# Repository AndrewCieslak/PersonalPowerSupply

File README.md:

# PersonalPowerSupply

My personal 20V in, 15-1.5 V out buck converter power supply code and schematics. Fully discrete, with almost no integrated components for the feedback loop.

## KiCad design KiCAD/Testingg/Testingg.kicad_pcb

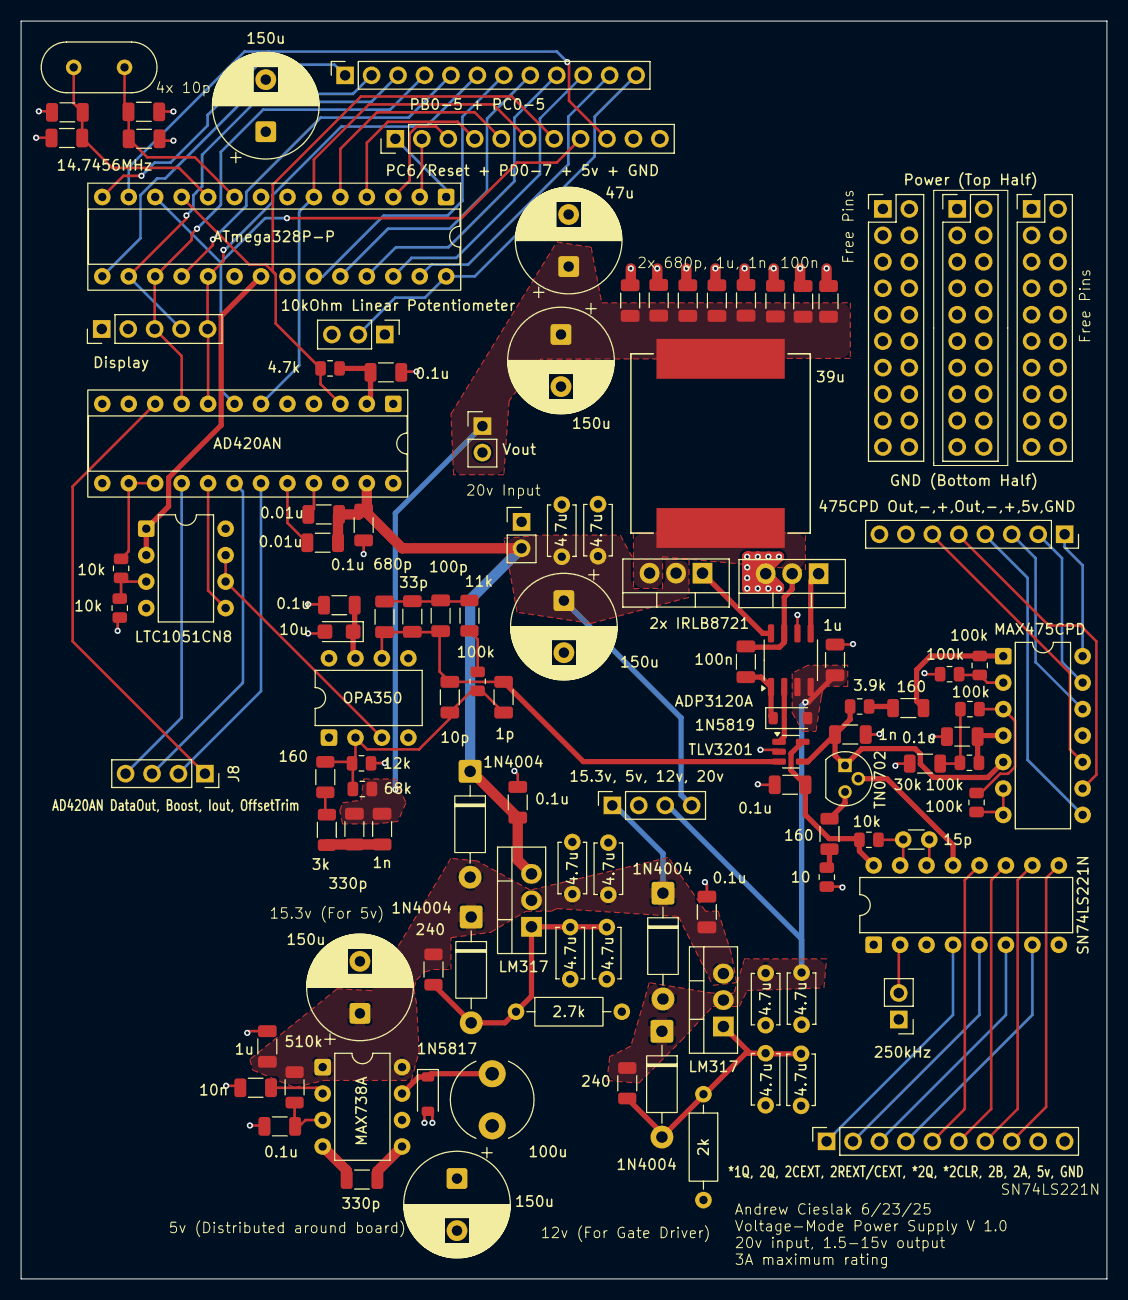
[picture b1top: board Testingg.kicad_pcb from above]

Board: 4 copper layers, 104.3 x 120.8 mm, 115 parts (0 on the bottom side), 84 nets.

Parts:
C1, C3, C8, C15, C16, C17, C22: 0.1u; C_1206_3216Metric
C2, C11, C12, C13, C18, C20, C21, C25: 4.7u; C_Disc_D4.7mm_W2.5mm_P5.00mm
C4: 330p; C_1206_3216Metric
C5, C10: 1u; C_1206_3216Metric
C6, C7, C14: 150u; CP_Radial_D10.0mm_P5.00mm
C9: 10n; C_1206_3216Metric
C19: 100n; C_1206_3216Metric
C23: 10u; CP_EIA-3216-10_Kemet-I
C24: 1n; C_1206_3216Metric
C26: 15p; C_Disc_D3.0mm_W1.6mm_P2.50mm
Cadnpo1, Cadnpo2: 0.01u; C_1206_3216Metric
Cbypass2: 0.1u; C_1206_3216Metric
Ccomp1: 100p; C_1206_3216Metric
Ccomp2: 33p; C_1206_3216Metric
Ccomp4: 680p; C_1206_3216Metric
Cff1: 1n; C_1206_3216Metric
Cff2: 330p; C_1206_3216Metric
Chf1: 10p; C_1206_3216Metric
Chf4: 1p; C_1206_3216Metric
Cin1, Cin2: 4.7u; C_Disc_D4.7mm_W2.5mm_P5.00mm
Cin3: 150u; CP_Radial_D10.0mm_P5.00mm
Cout1: 150u; CP_Radial_D10.0mm_P5.00mm
Cout2: 47u; CP_Radial_D10.0mm_P5.00mm
Cout3, Cout4: 1u; C_1206_3216Metric
Cout5, Cout6: 0.1u; C_1206_3216Metric
Cout7, Cout8: 1n; C_1206_3216Metric
Cout9, Cout10: 680p; C_1206_3216Metric
Cxtal1, Cxtal2, Cxtal3, Cxtal4: 10p; C_1206_3216Metric
D1: 1N5817; D_SOD-123
D2, D4, D5, D6: 1N4004; D_DO-41_SOD81_P10.16mm_Horizontal
D3: 1N5819; D_SOD-123
Display1: Display; PinHeader_1x05_P2.54mm_Vertical
J1: 10kOhm Linear Potentiometer; PinHeader_1x03_P2.54mm_Vertical
J2: 15.3v, 5v, 12v, 20v; PinSocket_1x04_P2.54mm_Vertical
J3: *1Q, 2Q, 2CEXT, 2REXT/CEXT, *2Q, *2CLR, 2B, 2A, 5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; PinSocket_1x10_P2.54mm_Vertical
J4: PB0-5 + PC0-5; PinSocket_1x12_P2.54mm_Vertical
J5: 250kHz; PinHeader_1x02_P2.54mm_Vertical
J6: Vin; PinHeader_1x02_P2.54mm_Vertical
J7: Breadboard; PinHeader_2x10_P2.54mm_Vertical
J8: AD420AN DataOut, Boost, Iout, OffsetTrim; PinSocket_1x04_P2.54mm_Vertical
J9: PC6/Reset + PD0-7 + 5v + GND; PinHeader_1x11_P2.54mm_Vertical
J10: 475CPD Out,-,+,Out,-,+,5v,GND; PinSocket_1x08_P2.54mm_Vertical
J11: Power (Top Half); PinHeader_2x10_P2.54mm_Vertical
J12: Breadboard2; PinHeader_2x10_P2.54mm_Vertical
L1: 100u; L_Radial_D7.8mm_P5.00mm_Fastron_07HCP
Lmain1: 39u; L_Vishay_IHLP-6767
Q1: IRLB8721PBF; TO-220-3_Vertical
Q2: 2x IRLB8721; TO-220-3_Vertical
R1, R4: 160; R_1206_3216Metric
R2: 10; R_0805_2012Metric
R3: 3.9k; R_0805_2012Metric
R5, R18, R19, R20, R21: 100k; R_0805_2012Metric
R6: 30k; R_1206_3216Metric
R7, R10: 240; R_1206_3216Metric
R8: 2.7k; R_Axial_DIN0207_L6.3mm_D2.5mm_P10.16mm_Horizontal
R9: 2k; R_Axial_DIN0207_L6.3mm_D2.5mm_P10.16mm_Horizontal
R14: 68k; R_0805_2012Metric
R15: 12k; R_0805_2012Metric
R16: 510k; R_1206_3216Metric
R24: 10k; R_0805_2012Metric
Rcomp1: 11k; R_1206_3216Metric
Rcomp3: 100k; R_0805_2012Metric
Rdiv1, Rdiv2: 10k; R_0805_2012Metric
Rff1: 160; R_1206_3216Metric
Rff2: 3k; R_1206_3216Metric
RpullupU6: 4.7k; R_0805_2012Metric
U1, U2: LM317; TO-220-3_Vertical
U3: ADP3120A; SO-8_3.9x4.9mm_P1.27mm
U4: OPA350; DIP-8_W7.62mm
U5: ATmega328P-P; DIP-28_W7.62mm_Socket
U6: AD420AN; DIP-24_W7.62mm_Socket
U7: LTC1051CN8; DIP-8_W7.62mm
U11: MAX738A; DIP-8_W7.62mm
U14: MAX475CPD; DIP-14_W7.62mm
U15: TN0702; TO-92
U17: SN74LS221N; DIP-16_W7.62mm
VM1: TLV3201; SOT-23-5
Vout1: Vout; PinHeader_1x02_P2.54mm_Vertical
Y1: 14.7456MHz; Crystal_HC49-U_Vertical

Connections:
+5V: C3.1, C4.2, C6.1, C14.1, C15.2, C22.1, C23.1, Cbypass2.1, Display1.1, J1.3, J2.2, J3.9, J9.10, J10.7, J11.1, J11.2, J11.3, J11.4, J11.5, J11.6, J11.7, J11.8, J11.9, J11.10, L1.2, R5.2, R24.1, RpullupU6.1, U4.7 (V+), U5.7 (VCC), U5.20 (AVCC), U6.2 (VLL), U7.8 (V+), U11.5 (OUT), U14.4 (V+), U17.3 (*1CLR), U17.16 (VCC), VM1.5 (VCC)
+20V: C16.2, C17.2, Cadnpo1.2, Cadnpo2.2, Cin1.1, Cin2.1, Cin3.1, D4.1 (K), J2.4, J6.2, Q2.2 (D), U1.3 (VI), U6.23 (VCC)
/J1: J4.1, U5.14 (PB0)
/J2: J4.2, U5.15 (PB1)
/J3: Display1.4, J4.3, U5.16 (PB2)
/J4: Display1.3, J4.4, U5.17 (PB3), U6.9 (DATA_IN)
/J5: J4.5, U5.18 (PB4)
/J6: Display1.5, J4.6, U5.19 (PB5), U6.8 (CLOCK)
/J9: J4.9, U5.25 (PC2)
/J10: J4.10, U5.26 (PC3)
/J11: J4.11, U5.27 (PC4)
/J12: J1.2, J4.12, U5.28 (PC5)
/VrefVM: U4.3 (IN+), U7.6 (IN_B-), U7.7 (OUT_B)
Earth: C1.1, C2.2, C3.2, C5.1, C6.2, C7.2, C8.1, C9.1, C10.2, C11.2, C12.2, C13.2, C14.2, C15.1, C16.1, C17.1, C18.2, C20.2, C21.2, C22.2, C23.2, C24.1, C25.2, Cbypass2.2, Cin1.2, Cin2.2, Cin3.2, Cout1.2, Cout2.2, Cout3.2, Cout4.2, Cout5.2, Cout6.2, Cout7.2, Cout8.2, Cout9.2, Cout10.2, Cxtal1.2, Cxtal2.2, Cxtal3.2, Cxtal4.2, D1.2 (A), Display1.2, J1.1, J3.10, J5.1, J6.1, J9.11, J10.8, J11.11, J11.12, J11.13, J11.14, J11.15, J11.16, J11.17, J11.18, J11.19, J11.20, Q1.3 (S), R2.1, R6.1, R8.2, R9.2, R15.2, R19.2, Rdiv2.1, U3.6 (PGND), U4.4 (V-), U5.8 (GND), U5.22 (GND), U6.4 (RANGE_SELECT2), U6.5 (RANGE_SELECT1), U6.11 (GND), U7.4 (V-), U11.6 (GND), U14.11 (V-), U17.1 (1A), U17.8 (GND), VM1.2 (GND), Vout1.2
unnamed: Ccomp1.2, Ccomp2.2, Ccomp4.2, Rcomp1.1
unnamed: Cff1.1, Cff2.1, Rff2.2
unnamed: D1.1 (K), L1.1, U11.7 (LX)
unnamed: C10.1, C12.1, C13.1, D2.2 (A), D3.2 (A), D6.1 (K), J2.3, R10.1, U2.2 (VO), U3.3 (*OD), U3.4 (VCC)
unnamed: C1.2, C5.2, C7.1, C21.1, C25.1, D2.1 (K), D4.2 (A), D5.1 (K), J2.1, R7.1, R16.1, U1.2 (VO), U2.3 (VI), U11.1 (*SHDN), U11.8 (V+)
unnamed: C19.2, D3.1 (K), U3.1 (BST)
unnamed: C18.1, C20.1, D5.2 (A), R7.2, R8.1, U1.1 (ADJ)
unnamed: C2.1, C11.1, D6.2 (A), R9.1, R10.2, U2.1 (ADJ)
unnamed: J3.1, U17.4 (*1Q)
unnamed: J3.2, U17.5 (2Q)
unnamed: J3.3, U17.6 (2CEXT)
unnamed: J3.4, U17.7 (2REXT/CEXT)
unnamed: J3.5, U17.12 (*2Q)
unnamed: J3.6, U17.11 (*2CLR)
unnamed: J3.7, U17.10 (2B)
unnamed: J3.8, U17.9 (2A)
unnamed: J4.7, U5.23 (PC0)
unnamed: J4.8, U5.24 (PC1)
unnamed: J5.2, U17.2 (1B)
unnamed: J8.1, U6.10 (DATA_OUT)
unnamed: J8.2, U6.19 (BOOST)
unnamed: J8.3, U6.18 (IOUT)
unnamed: J8.4, U6.16 (OFFSET_TRIM)
unnamed: J9.1, U5.1 (~RESET/PC6)
unnamed: J9.2, U5.2 (PD0)
unnamed: J9.3, U5.3 (PD1)
unnamed: J9.4, U5.4 (PD2)
unnamed: J9.5, U5.5 (PD3)
unnamed: J9.6, U5.6 (PD4), U6.6 (CLEAR)
unnamed: J9.7, RpullupU6.2, U5.11 (PD5), U6.3 (FAULT_DETECT)
unnamed: J9.8, U5.12 (PD6), U6.7 (LATCH)
unnamed: J9.9, U5.13 (PD7)
unnamed: J10.1, U14.14 (OUT)
unnamed: J10.2, U14.13 (-)
unnamed: J10.3, U14.12 (+)
unnamed: J10.4, U14.8 (OUT)
unnamed: J10.5, U14.9 (-)
unnamed: J10.6, U14.10 (+)
unnamed: C19.1, Lmain1.1, Q1.2 (D), Q2.3 (S), U3.7 (SWN)
unnamed: Q1.1 (G), U3.5 (DRVL)
unnamed: Q2.1 (G), U3.8 (DRVH)
unnamed: R1.1, R2.2
unnamed: R3.1, R4.1
unnamed: R18.1, R19.1, U14.2 (-)
unnamed: R4.2, R18.2, U14.1 (OUT)
unnamed: R5.1, R6.2, R20.1
unnamed: R20.2, R21.2, U14.3 (+)
unnamed: R21.1, U14.6 (-), U14.7 (OUT)
unnamed: Rcomp1.2, Rcomp3.1
unnamed: Rff1.2, Rff2.1
unnamed: U3.2 (IN), VM1.1 (OUT)
unnamed: Chf1.2, Chf4.2, R14.1, R15.1, Rcomp3.2, Rff1.1, U4.2 (IN-)
unnamed: Ccomp1.1, Ccomp2.1, Ccomp4.1, Chf1.1, Chf4.1, U4.6 (OUTPUT), VM1.3 (IN+)
unnamed: U5.21 (AREF), U7.1 (OUT_A), U7.2 (IN_A-)
unnamed: Cxtal2.1, Cxtal3.1, U5.9 (XTAL1/PB6), Y1.2
unnamed: Cxtal1.1, Cxtal4.1, U5.10 (XTAL2/PB7), Y1.1
unnamed: Cadnpo1.1, U6.20 (CAP1)
unnamed: Cadnpo2.1, U6.21 (CAP2)
unnamed: Rdiv1.2, U6.14 (REF_OUT), U6.15 (REF_IN)
unnamed: U6.17 (VOUT), U7.5 (IN_B+)
unnamed: Rdiv1.1, Rdiv2.2, U7.3 (IN_A+)
unnamed: C4.1, U11.4 (CC)
unnamed: C9.2, U11.2 (REF)
unnamed: C8.2, R16.2, U11.3 (SS)
unnamed: R1.2, U15.3 (DRAIN)
unnamed: U15.2 (GATE), U17.13 (1Q)
unnamed: C24.2, R3.2, U14.5 (+), U15.1 (SOURCE), VM1.4 (IN-)
unnamed: C26.1, U17.14 (1CEXT)
unnamed: C26.2, R24.2, U17.15 (1REXT/CEXT)
unnamed: Cff1.2, Cff2.2, Cout1.1, Cout2.1, Cout3.1, Cout4.1, Cout5.1, Cout6.1, Cout7.1, Cout8.1, Cout9.1, Cout10.1, Lmain1.2, R14.2, Vout1.1

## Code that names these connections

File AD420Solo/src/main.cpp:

#include <avr/io.h>
#include <util/delay.h>
#include <stdint.h>

#include "pins.h"
#include "uart.h"



int main(void){

  uart_init();
  
  //LEDs
  DDRD |= (1<<PD2) | (1<<PD3) | (1<<PD5);
  PORTD &= ~((1<<PD2) | (1<<PD3) | (1<<PD5));
  //blue LED ON
  PORTD |= (1<<PD2);

  DDRB  |= (1<<PB3) | (1<<PB5);
  PORTB |= (1<<PB2);
  SPCR = (1<<SPE) | (1<<MSTR);
  SPSR = 0;   
  AD420_CLR_DDR |= (1<<CLR_AD420);
  AD420_CLR_PORT &= ~(1<<CLR_AD420);
  // SPI init

  AD420_CLR_PORT |=  (1<<CLR_AD420);   // CLEAR = 1
  _delay_us(1); // delay >50ns
  AD420_CLR_PORT &= ~(1<<CLR_AD420);   // CLEAR = 0

  uint16_t voltmv = 1000;

  //white LED
  PORTD |= (1<<PD3);  
  //   Converts a desired voltage (0…5000 mV) to a 16-bit DAC code (0…0xFFFF).
  if (voltmv > 5000) voltmv = 5000;
  uint32_t temp = (uint32_t)voltmv * 65535;
  uint16_t code = (uint16_t)(temp / 5000);
  // turns into binary
  uint16_t high_byte =  (uint8_t)(code >> 8);
  // top 8-bits
  uint16_t low_byte = (uint8_t)(code & 0xFF);
  // bottom 8-bits saved
  AD420_CS_PORT &= ~(1<<CS_AD420);
  // start frame
  SPI_DATA = high_byte;
  // begins transfer of byte
  while(!(SPI_STATUS & (1<<SPI_TRANSFER_FLAG)));
  // (spif location, not its status, is in the variable SPIF. the register is volatile and changes, while the bit location is constant)
  // if and only if xxxxxxxx & x0000000 results in 1 does it pass, since last 7 bits always 0, and first just depends on if status is actually 1 or 0
  // the ! is because while loops repeat when true (1), so the exit condition is 0 and must use !.
  (void)SPI_DATA;           
  // reading SPDR clears SPIF
  SPI_DATA = low_byte;
  // begins transfer
  while(!(SPI_STATUS & (1<<SPI_TRANSFER_FLAG)));
  // sends
  (void)SPI_DATA;       
  // acknowledged
  AD420_CS_PORT |= (1<<CS_AD420);
  // LATCH = 1, dumping 16 bits into ad420 immediately after byte sent
  _delay_us(1);
  // AVR-GCC intrinsic function, CPU cycles
  AD420_CS_PORT |= (1<<CS_AD420);
  // LATCH = 1, resetting for next input
  _delay_us(1);
  
  uart_transmit_string("transmitted");
  while(1);
}
